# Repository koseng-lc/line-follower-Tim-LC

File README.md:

# Line Follower

This is my personal robot. The development started at the end of 2016 and discontinued in mid-2017.

### Photos

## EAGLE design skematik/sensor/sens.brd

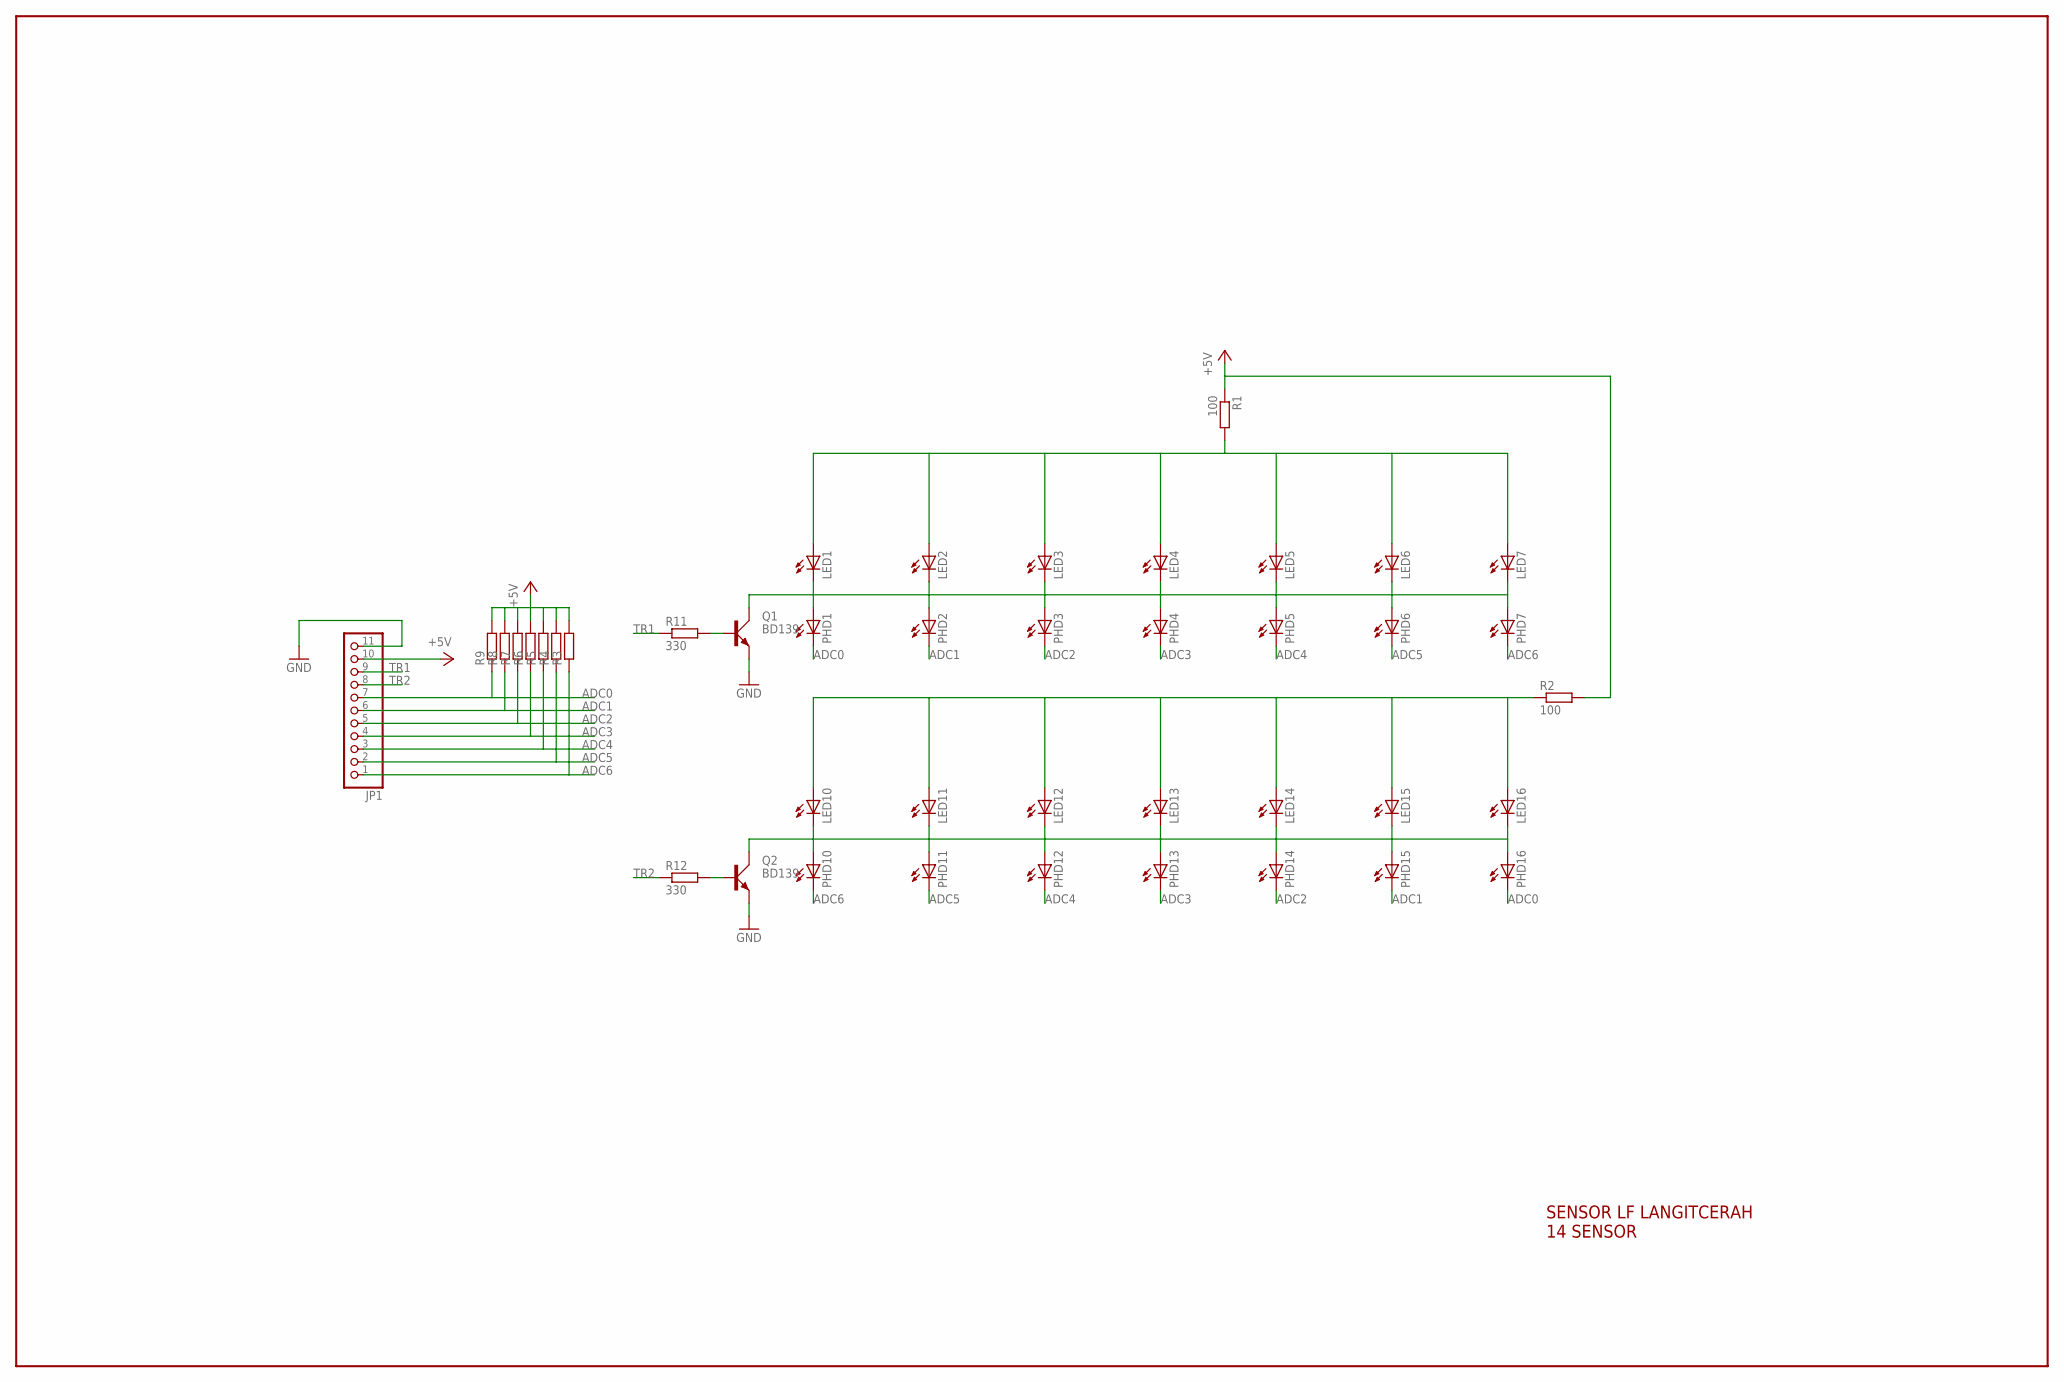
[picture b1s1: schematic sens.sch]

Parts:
JP1: PINHD-1X11; 1X11
LED1, LED2, LED3, LED4, LED5, LED6, LED7, LED10, LED11, LED12, LED13, LED14, LED15, LED16: LED3MM
PHD1, PHD2, PHD3, PHD4, PHD5, PHD6, PHD7, PHD10, PHD11, PHD12, PHD13, PHD14, PHD15, PHD16: LED3MM
Q1, Q2: BD139; TO126AV
R1, R2: 100; 0207/10
R3, R4, R5, R6, R7, R8, R9: R-EU_0207/10; 0207/10
R11, R12: 330; 0207/10

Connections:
+5V: JP1.10, R1.1, R2.2, R3.2, R4.2, R5.2, R6.2, R7.2, R8.2, R9.2
ADC0: JP1.7, PHD1.K (C), PHD16.K (C), R9.1
ADC1: JP1.6, PHD2.K (C), PHD15.K (C), R8.1
ADC2: JP1.5, PHD3.K (C), PHD14.K (C), R7.1
ADC3: JP1.4, PHD4.K (C), PHD13.K (C), R6.1
ADC4: JP1.3, PHD5.K (C), PHD12.K (C), R5.1
ADC5: JP1.2, PHD6.K (C), PHD11.K (C), R4.1
ADC6: JP1.1, PHD7.K (C), PHD10.K (C), R3.1
GND: JP1.11, Q1.E, Q2.E
unnamed: LED1.A, LED2.A, LED3.A, LED4.A, LED5.A, LED6.A, LED7.A, R1.2
unnamed: LED1.K (C), LED2.K (C), LED3.K (C), LED4.K (C), LED5.K (C), LED6.K (C), LED7.K (C), PHD1.A, PHD2.A, PHD3.A, PHD4.A, PHD5.A, PHD6.A, PHD7.A, Q1.C
unnamed: LED10.K (C), LED11.K (C), LED12.K (C), LED13.K (C), LED14.K (C), LED15.K (C), LED16.K (C), PHD10.A, PHD11.A, PHD12.A, PHD13.A, PHD14.A, PHD15.A, PHD16.A, Q2.C
unnamed: Q1.B, R11.2
unnamed: Q2.B, R12.2
TEPI: LED10.A, LED11.A, LED12.A, LED13.A, LED14.A, LED15.A, LED16.A, R2.1
TR1: JP1.9, R11.1
TR2: JP1.8, R12.1

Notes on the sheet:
SENSOR LF LANGITCERAH 14 SENSOR

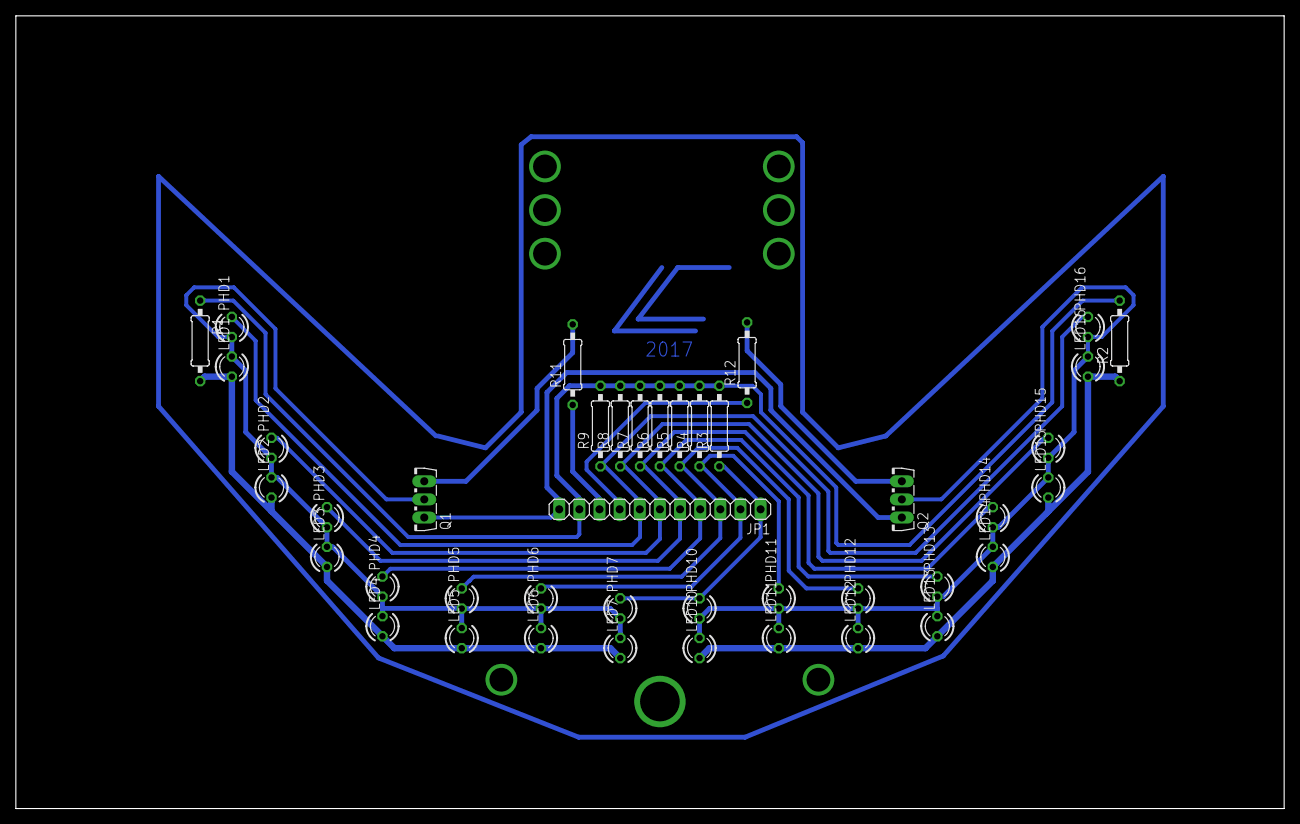
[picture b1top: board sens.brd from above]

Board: 2 copper layers, 160.0 x 100.0 mm, 42 parts (0 on the bottom side), 17 nets.

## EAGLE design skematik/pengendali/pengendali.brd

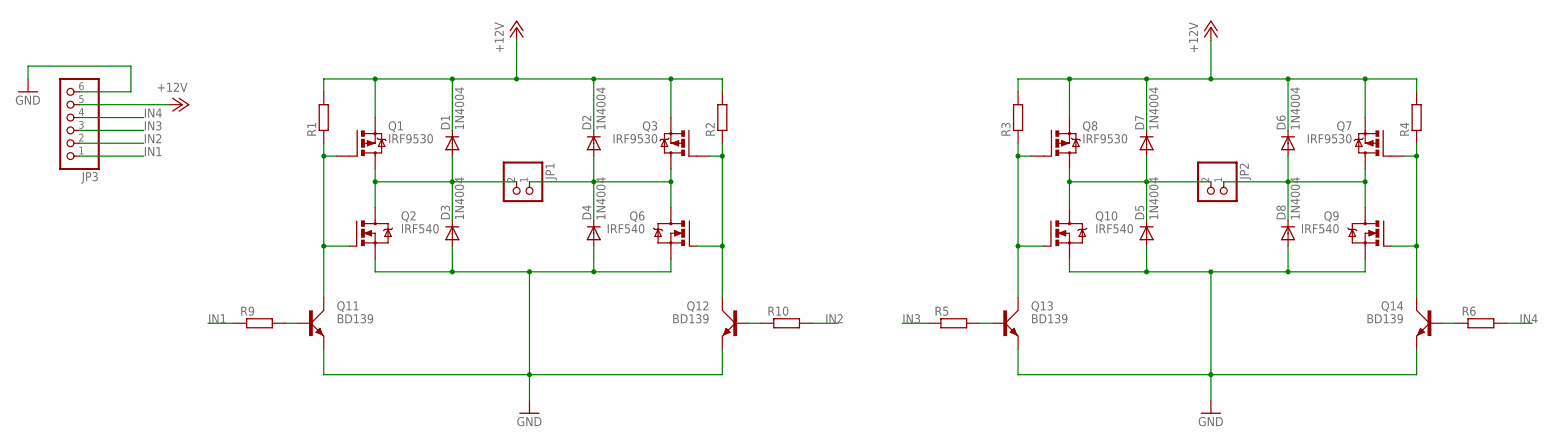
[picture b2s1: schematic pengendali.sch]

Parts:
D1, D2, D3, D4, D5, D6, D7, D8: 1N4004; DO41-10
JP1, JP2: PINHD-1X2; 1X02
JP3: PINHD-1X6; 1X06
Q1, Q3, Q7, Q8: IRF9530; TO220BV
Q2, Q6, Q9, Q10: IRF540; TO220BV
Q11, Q12, Q13, Q14: BD139; TO126AV
R1, R2, R3, R4, R5, R6, R9, R10: R-EU_0204/7; 0204/7

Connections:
+12V: D1.C, D2.C, D6.C, D7.C, JP3.5, Q1.S, Q3.S, Q7.S, Q8.S, R1.2, R2.2, R3.2, R4.2
GND: D3.A, D4.A, D5.A, D8.A, JP3.6, Q2.S, Q6.S, Q9.S, Q10.S, Q11.E, Q12.E, Q13.E, Q14.E
IN1: JP3.1, R9.1
IN2: JP3.2, R10.2
IN3: JP3.3, R5.1
IN4: JP3.4, R6.2
unnamed: Q1.G, Q2.G, Q11.C, R1.1
unnamed: Q8.G, Q10.G, Q13.C, R3.1
unnamed: Q3.G, Q6.G, Q12.C, R2.1
unnamed: Q11.B, R9.2
unnamed: Q12.B, R10.1
unnamed: D1.A, D3.C, JP1.2, Q1.D, Q2.D
unnamed: D2.A, D4.C, JP1.1, Q3.D, Q6.D
unnamed: Q13.B, R5.2
unnamed: Q14.B, R6.1
unnamed: Q7.G, Q9.G, Q14.C, R4.1
unnamed: D5.C, D7.A, JP2.2, Q8.D, Q10.D
unnamed: D6.A, D8.C, JP2.1, Q7.D, Q9.D

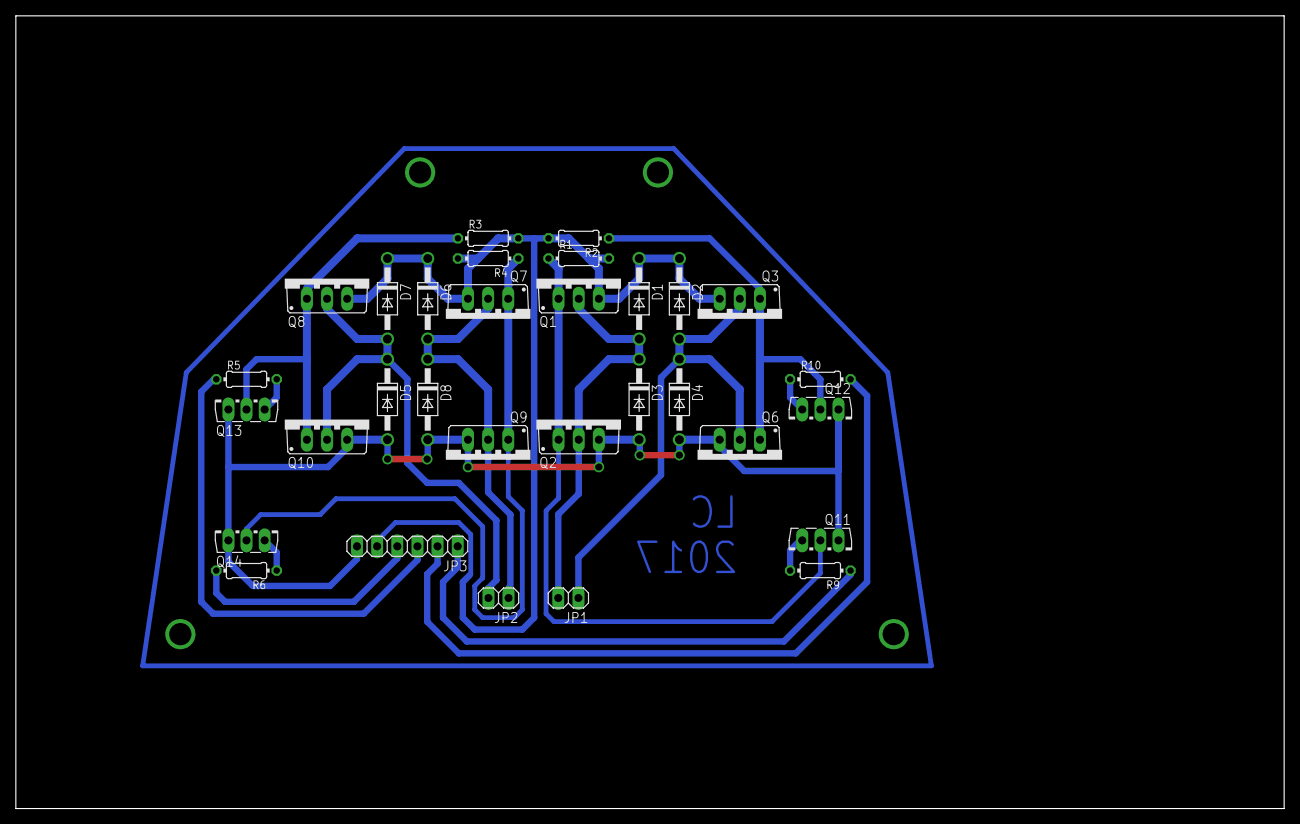
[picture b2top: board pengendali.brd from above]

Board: 2 copper layers, 160.0 x 100.0 mm, 31 parts (0 on the bottom side), 18 nets.

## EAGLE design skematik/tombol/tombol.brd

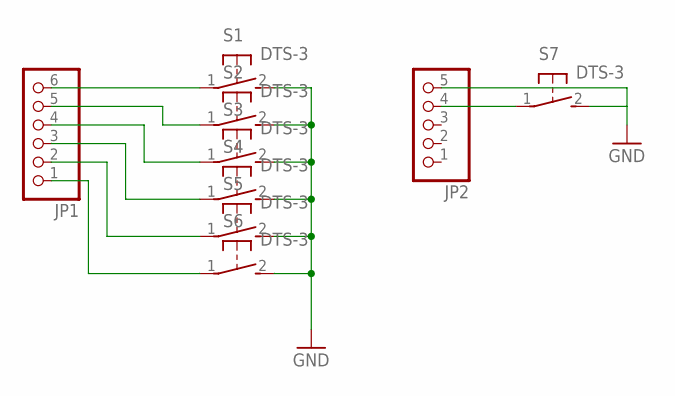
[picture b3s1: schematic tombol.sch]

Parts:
JP1: PINHD-1X6; 1X06
JP2: PINHD-1X5; 1X05
S1, S2, S3, S4, S5, S6, S7: DTS-3

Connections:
GND: JP2.5, S1.2, S2.2, S3.2, S4.2, S5.2, S6.2, S7.2
unnamed: JP1.6, S1.1
unnamed: JP1.5, S2.1
unnamed: JP1.4, S3.1
unnamed: JP1.3, S4.1
unnamed: JP1.2, S5.1
unnamed: JP1.1, S6.1
unnamed: JP2.4, S7.1

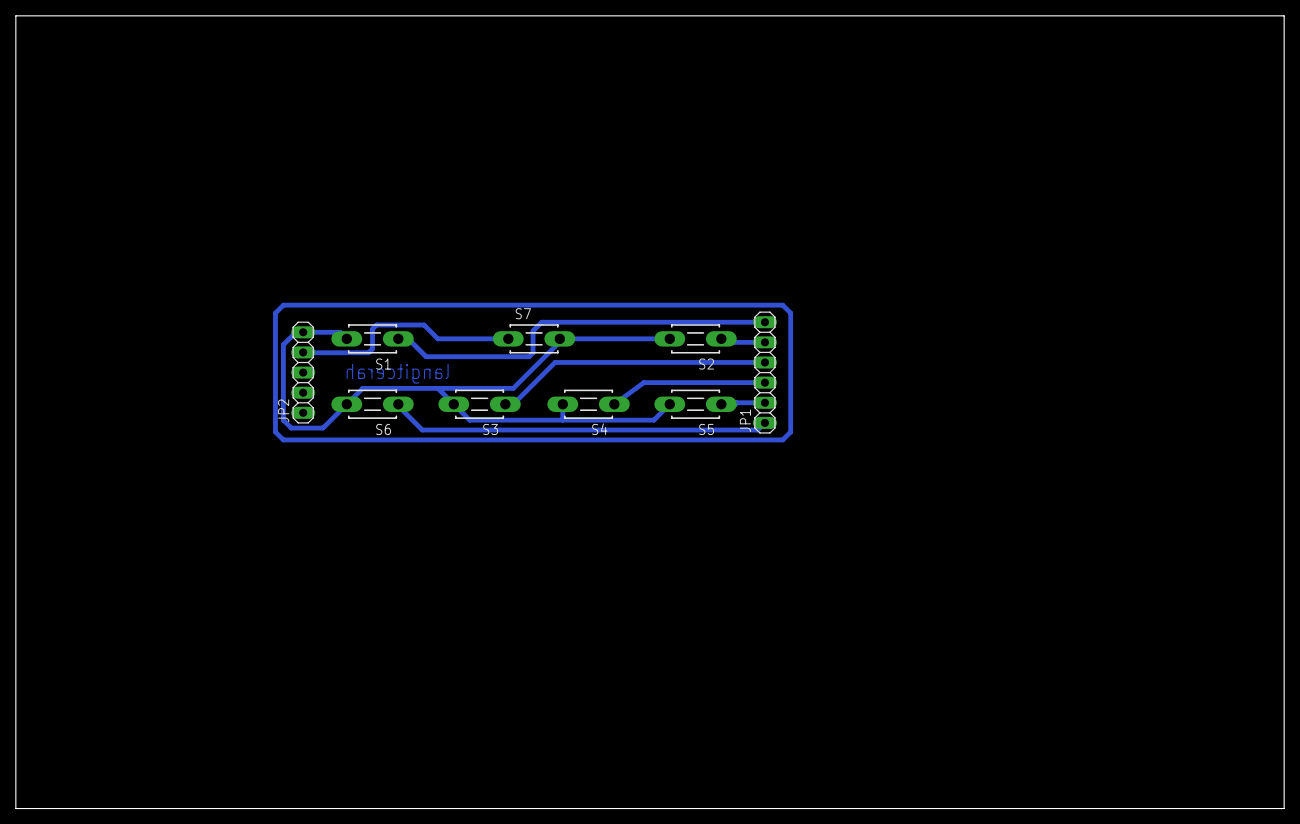
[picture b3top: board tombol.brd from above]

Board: 2 copper layers, 160.0 x 100.0 mm, 9 parts (0 on the bottom side), 8 nets.

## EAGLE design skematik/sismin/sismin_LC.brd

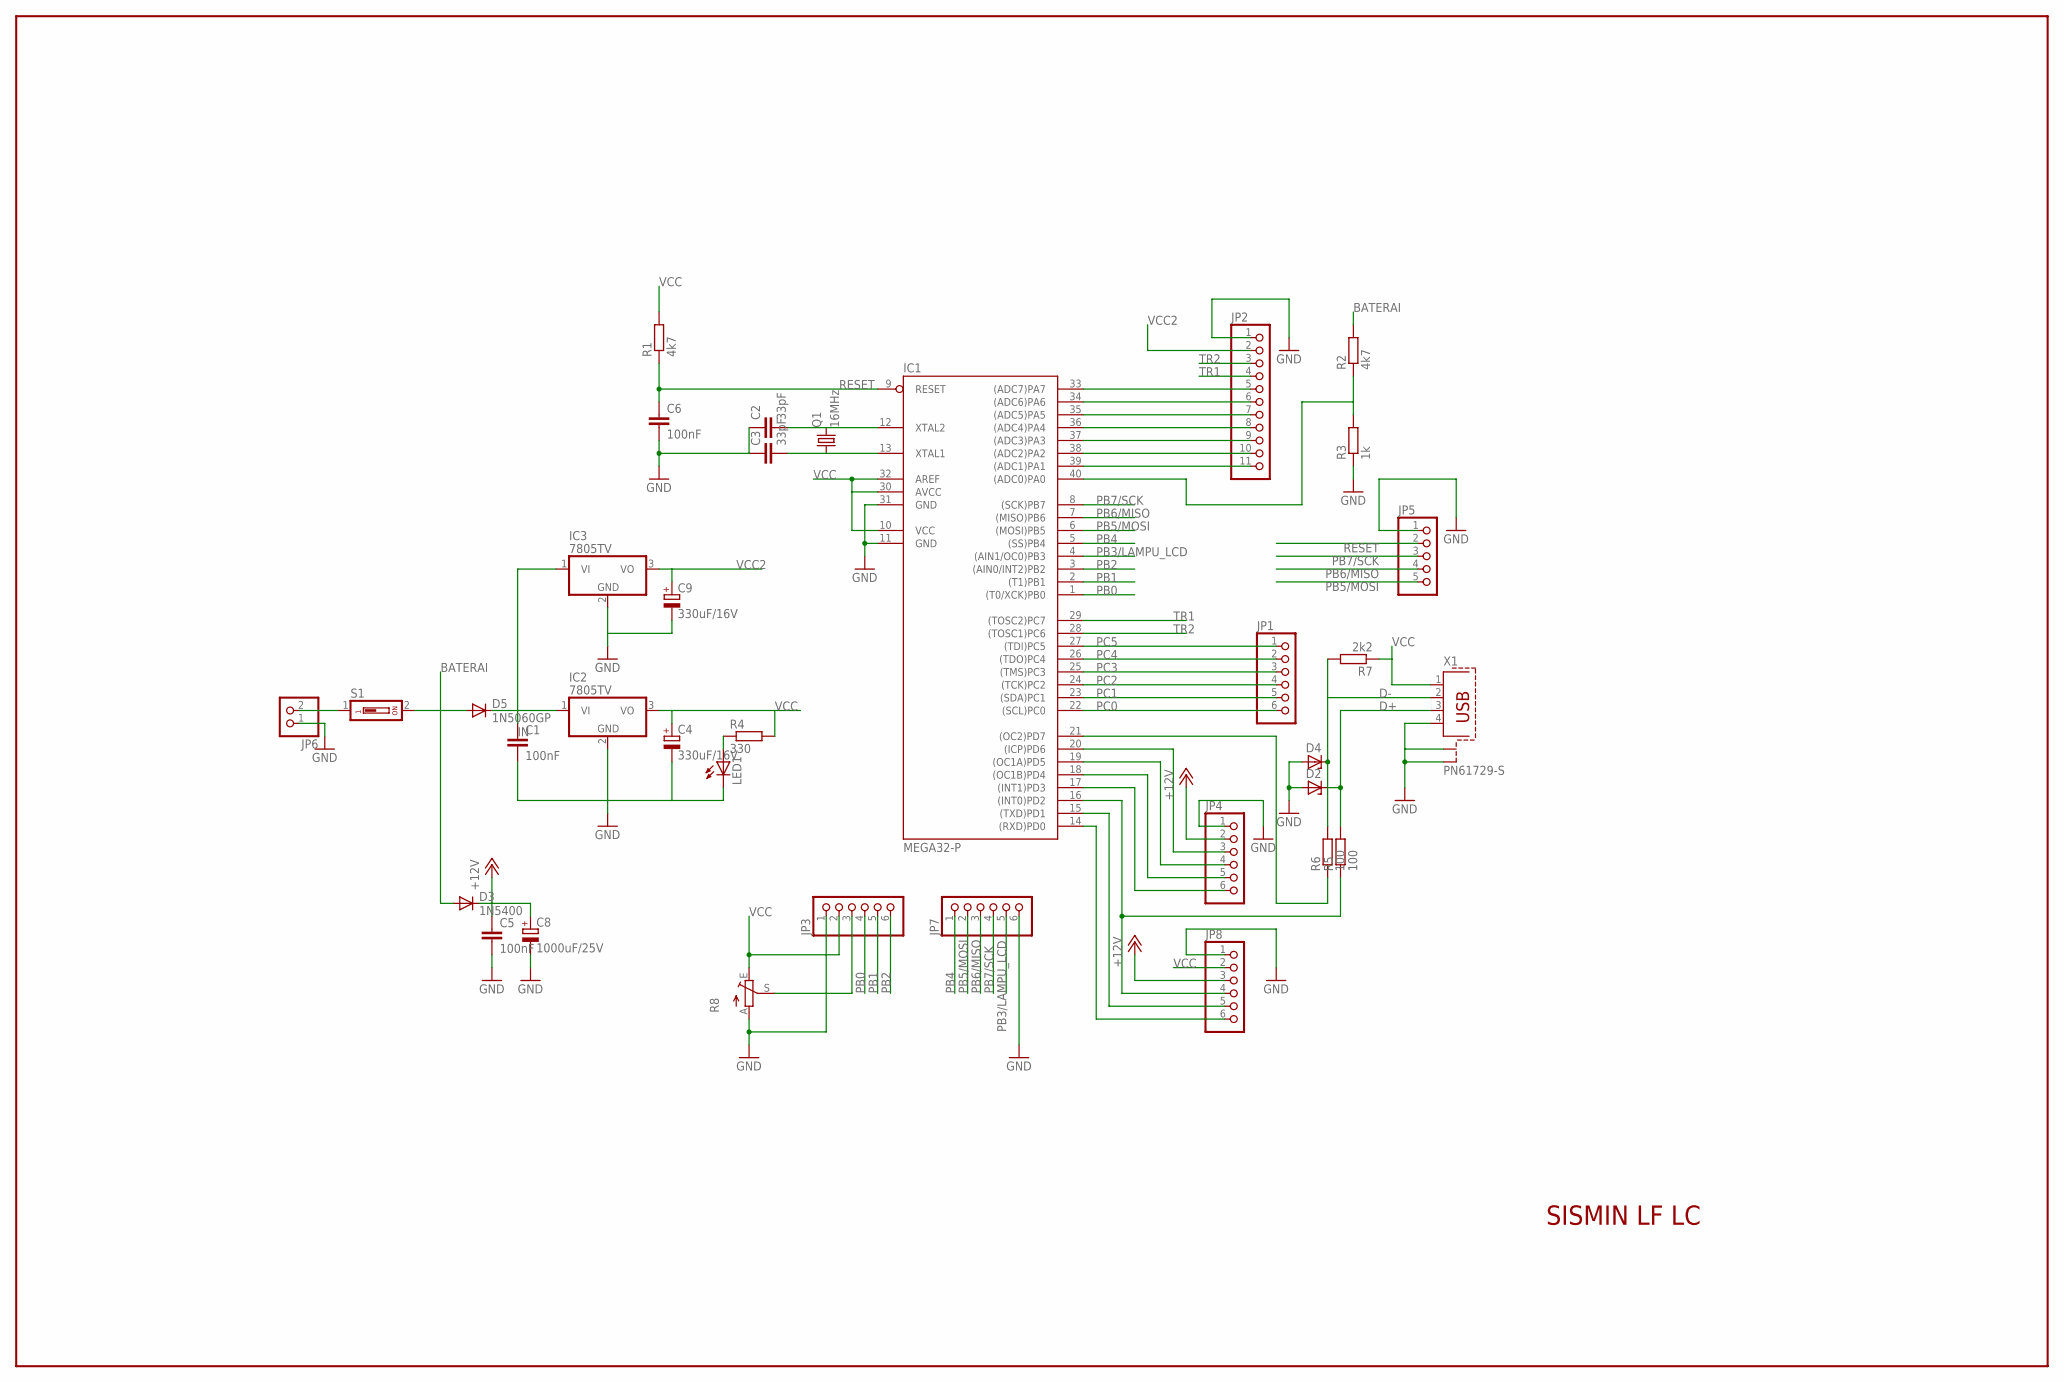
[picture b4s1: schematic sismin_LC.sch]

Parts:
C1, C5, C6: 100nF; C050-025X075
C2, C3: 33pF; C025-025X050
C4, C9: 330uF/16V; E2-5
C8: 1000uF/25V; E2,5-6
D2, D4: ZENER-DIODEDO41Z10; DO41Z10
D3: 1N5400; DO201-15
D5: 1N5060GP; DO15-12
IC1: MEGA32-P; DIL40
IC2, IC3: 7805TV; TO220V
JP1, JP3, JP4, JP7, JP8: PINHD-1X6; 1X06
JP2: PINHD-1X11; 1X11
JP5: PINHD-1X5; 1X05
JP6: PINHD-1X2; 1X02
LED1: LED3MM
Q1: 16MHz; HC49/S
R1, R2: 4k7; 0204/7
R3: 1k; 0204/7
R4: 330; 0204/7
R5, R6: 100; 0204/7
R7: 2k2; 0204/7
R8: TRIM_EU-RS3; RS3
S1: DS01; DS-01
X1: PN61729-S

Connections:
+12V: C5.1, C8.+, D3.C, JP4.2, JP8.3
ADC1: IC1.39 ((ADC1)PA1), JP2.11
ADC2: IC1.38 ((ADC2)PA2), JP2.10
ADC3: IC1.37 ((ADC3)PA3), JP2.9
ADC4: IC1.36 ((ADC4)PA4), JP2.8
ADC5: IC1.35 ((ADC5)PA5), JP2.7
ADC6: IC1.34 ((ADC6)PA6), JP2.6
ADC7: IC1.33 ((ADC7)PA7), JP2.5
BATERAI: D3.A, D5.A, R2.2, S1.2
D+: D2.C, R5.2, X1.3
D-: D4.C, R6.2, R7.2, X1.2
GND: C1.2, C2.1, C3.1, C4.-, C5.2, C6.2, C8.-, C9.-, D2.A, D4.A, IC1.11 (GND), IC1.31 (GND), IC2.2 (GND), IC3.2 (GND), JP2.1, JP3.1, JP4.1, JP5.1, JP6.1, JP7.6, JP8.1, LED1.K (C), R3.1, R8.A, X1.4, X1.S1, X1.S2
IN: C1.1, D5.C, IC2.1 (VI), IC3.1 (VI)
unnamed: C2.2, IC1.12 (XTAL2), Q1.2
unnamed: C3.2, IC1.13 (XTAL1), Q1.1
unnamed: IC1.40 ((ADC0)PA0), R2.1, R3.2
unnamed: JP6.2, S1.1
unnamed: LED1.A, R4.1
unnamed: IC1.16 ((INT0)PD2), JP8.4, R5.1
unnamed: IC1.20 ((ICP)PD6), JP4.3
unnamed: IC1.19 ((OC1A)PD5), JP4.4
unnamed: IC1.18 ((OC1B)PD4), JP4.5
unnamed: IC1.17 ((INT1)PD3), JP4.6
unnamed: JP3.3, R8.S
unnamed: IC1.21 ((OC2)PD7), R6.1
PB0: IC1.1 ((T0/XCK)PB0), JP3.4
PB1: IC1.2 ((T1)PB1), JP3.5
PB2: IC1.3 ((AIN0/INT2)PB2), JP3.6
PB3/LAMPU_LCD: IC1.4 ((AIN1/OC0)PB3), JP7.5
PB4: IC1.5 ((SS)PB4), JP7.1
PB5/MOSI: IC1.6 ((MOSI)PB5), JP5.5, JP7.2
PB6/MISO: IC1.7 ((MISO)PB6), JP5.4, JP7.3
PB7/SCK: IC1.8 ((SCK)PB7), JP5.3, JP7.4
PC0: IC1.22 ((SCL)PC0), JP1.6
PC1: IC1.23 ((SDA)PC1), JP1.5
PC2: IC1.24 ((TCK)PC2), JP1.4
PC3: IC1.25 ((TMS)PC3), JP1.3
PC4: IC1.26 ((TDO)PC4), JP1.2
PC5: IC1.27 ((TDI)PC5), JP1.1
RESET: C6.1, IC1.9 (RESET), JP5.2, R1.1
RX: IC1.14 ((RXD)PD0), JP8.6
TR1: IC1.29 ((TOSC2)PC7), JP2.4
TR2: IC1.28 ((TOSC1)PC6), JP2.3
TX: IC1.15 ((TXD)PD1), JP8.5
VCC: C4.+, IC1.10 (VCC), IC1.30 (AVCC), IC1.32 (AREF), IC2.3 (VO), JP3.2, JP8.2, R1.2, R4.2, R7.1, R8.E, X1.1
VCC2: C9.+, IC3.3 (VO), JP2.2

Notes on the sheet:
SISMIN LF LC

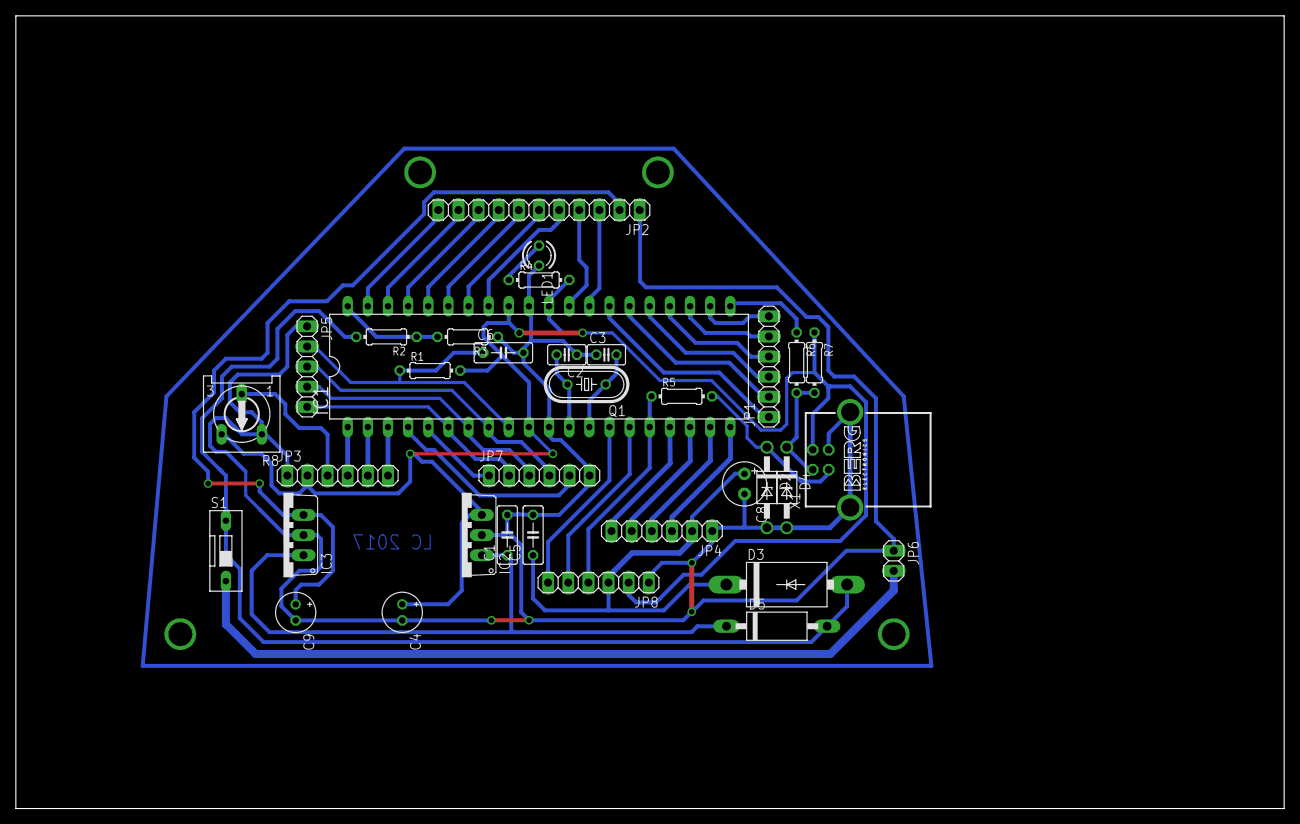
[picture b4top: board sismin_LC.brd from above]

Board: 2 copper layers, 160.0 x 100.0 mm, 35 parts (0 on the bottom side), 46 nets.

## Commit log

2019-11-02 add photos
